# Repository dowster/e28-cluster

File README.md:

# E28 Cluster Driver

E28 Cluster Driver is (going to be...) an ESP32 based driver board which allows the E28, and possibly E21/E30, cluster to be controlled via custom inputs. For the first version custom input will be done solely via CAN Bus. There won't be any hardcoded message spec, that will be configurable by the user after firmware has been flashed. 

> Main repository is at https://gitlab.com/dowster/e28-cluster

# Build Status

## Hardware

- ESP32
- [GD32VF103RBT6](https://www.mouser.com/ProductDetail/GigaDevice/GD32VF103RBT6)

# ESP IDF Version
v4.2

:)

# E28 Cluster Driver Inputs

Input to the E28 cluster driver shall be done via CAN Bus and possibly with a web based interface for diagnostics, calibration, and configuration. The CAN input shall be configurable so that any value on a can message may be mapped to any of the outputs, allowing the potential for configuring the driver with custom cluster gauge faces. IE: using the econometer to show watts / mile. 

# Instrument Cluster Outputs

## Speedometer Output

The speedometer of the E28 cluster is pulse driven. Approximately 2Hz for every MPH. IE: 50hz -> 25mph, 280hz -> 140mph. Driving the speedometer will advance the odometer automatically. It will also generate a pulse signal that is output to the SI board and the cruise control hardware. 

The speedometer operates on a [UAF 2115 IC](https://darisusgmbh.de/darisus/Elektonikshop/Datenblaetter/ITT/UAF2115.pdf). This IC is a general purpose speedoemter and mileage indidactor IC by ITT Semiconductors. It provides a constant current source to the output pin(s) 10-13 on the E28 cluster plug C2 (white), these four pins are all bridged together, shorting these to ground will provide a pulse to the speedometer. The UAF 2115 also provides an open collector NPN pulse output to drive things such as cruise control. In order to trigger a pulse the speed sensor in the differential would short to ground as each tooth of the gear passed by, these pulses must be atleast 50 microseconds in duration, the max frequency is 10Khz. On the E28 Pin 11 of UAF 2115 is connected to ground, so the division factor is 2^6, I think this is to configure how the odometer tracks distance. 

## Temperature Gauge Output

The temperature guage output will be an open collector NPN output from the E28 cluster driver. The temperature gauge is controlled by varying the current output of pin 12 on connector C1 of the E28 instrument cluster. To control this I'll either use the DAC on the ESP32 or use PWM. I have had some issues with "buzzing" when using PWM but I may just need a higher frequency. 

## Fuel Gauge Output

This is pretty much the same as the temperature gauge but with a different calibration. I'll be using a lower value resistor on the gate of this transistor since the fuel gauge requires more current. This signal is also output to the onboard computer by default. See [OBC Outputs](#OBC-Outputs) for information on how I plan to control the OBC.

## Tachometer Output

The tachometer is controleld by a simple voltage input. I'm thinking a PNP driver for this with PWM control should be fine. 

## Econometer Output

No clue how to do this one yet, haven't really looked into it. 

## Warning Indicators (On PCB)

The warning lights will be controlled via simple solid state relay circuits. Either PNP or NPN transistors controleld via shift registers to save up some pins on the ESP32, if needed. Some of the warning indicators are built onto the instrument cluster's PCB, others are controlled via lights have external wiring. 

### Charge Indicator

Could have many different functions, possibly solid when charging the pack or when the pre-charge resistor is engaged and flashing when a pack error is detected.

### Brake Warning Indicator

TODO

### High Beam Indicator

TODO

### Fog Light Indicator

TODO

### LH Turn Indicator

TODO

### RH Turn Indicator

TODO

### Low Fuel Warning Indicator 

TODO

### "Check" Active Check Control Alarm Indicator

TODO

### Oil Pressure Warning Indicator

This is probably not needed with an EV so that could be modified to be _something else_.

### "Park Brake" Indicator

TODO

### Brake Lining indicator

Haven't seen how this wires up yet, It's on the PCB.

## Warning Indicators (External Wiring)

### Left and Right turn arrows

Probably used to be used on cars where there was only one lamp to tell you that the turn indicators were on. Could be repurposed with a different logo. Background is green.

### Solid Yellow

There's no graphic on this lamp, it's in the 3rd position from left and just has a yellow or orange color filter. 

### EML

Not wired up, says "EML" in black letters with a yellow or orange color filter. 4th position from left

### Solid Green

No graphic on this indiactor, just a solid green. 6th position from left.

### ABS

If the stock ABS is kept this can stay here. Not sure if ABS is used on many swaps but I think that if it is this light may want to be used as a way to kill regen and let the motor coast while ABS figures out what to do. 

## Gearshift Indicators

Seems like even the manual clusters include this plate, or my car has been swapped with an automatic cluster. 

### Transmission Warning Indicator

Shows as a gear with an exclamation mark in the center

### P, R, N, D

Pretty self explanatory

### 3, 2, 1

Show up as individual lamps, for indicating if you've manually selected one of these gears I presume. 

### 1-2-3

This is on single indicator, I presume that it indicates you've disabled overdrive. 

# OBC Outputs

The method for driving the OBC hasn't been determined yet, two options are to just plug the OBC into the instrument cluster and let it run business as usual. The more involved, and possibly better method is to map out the pins on the OBC and manipulate that with the  E28 cluster driver. The main feature I'd like to see out of this is an accuruate range estimate based on pack state of charge and average watts/mile.

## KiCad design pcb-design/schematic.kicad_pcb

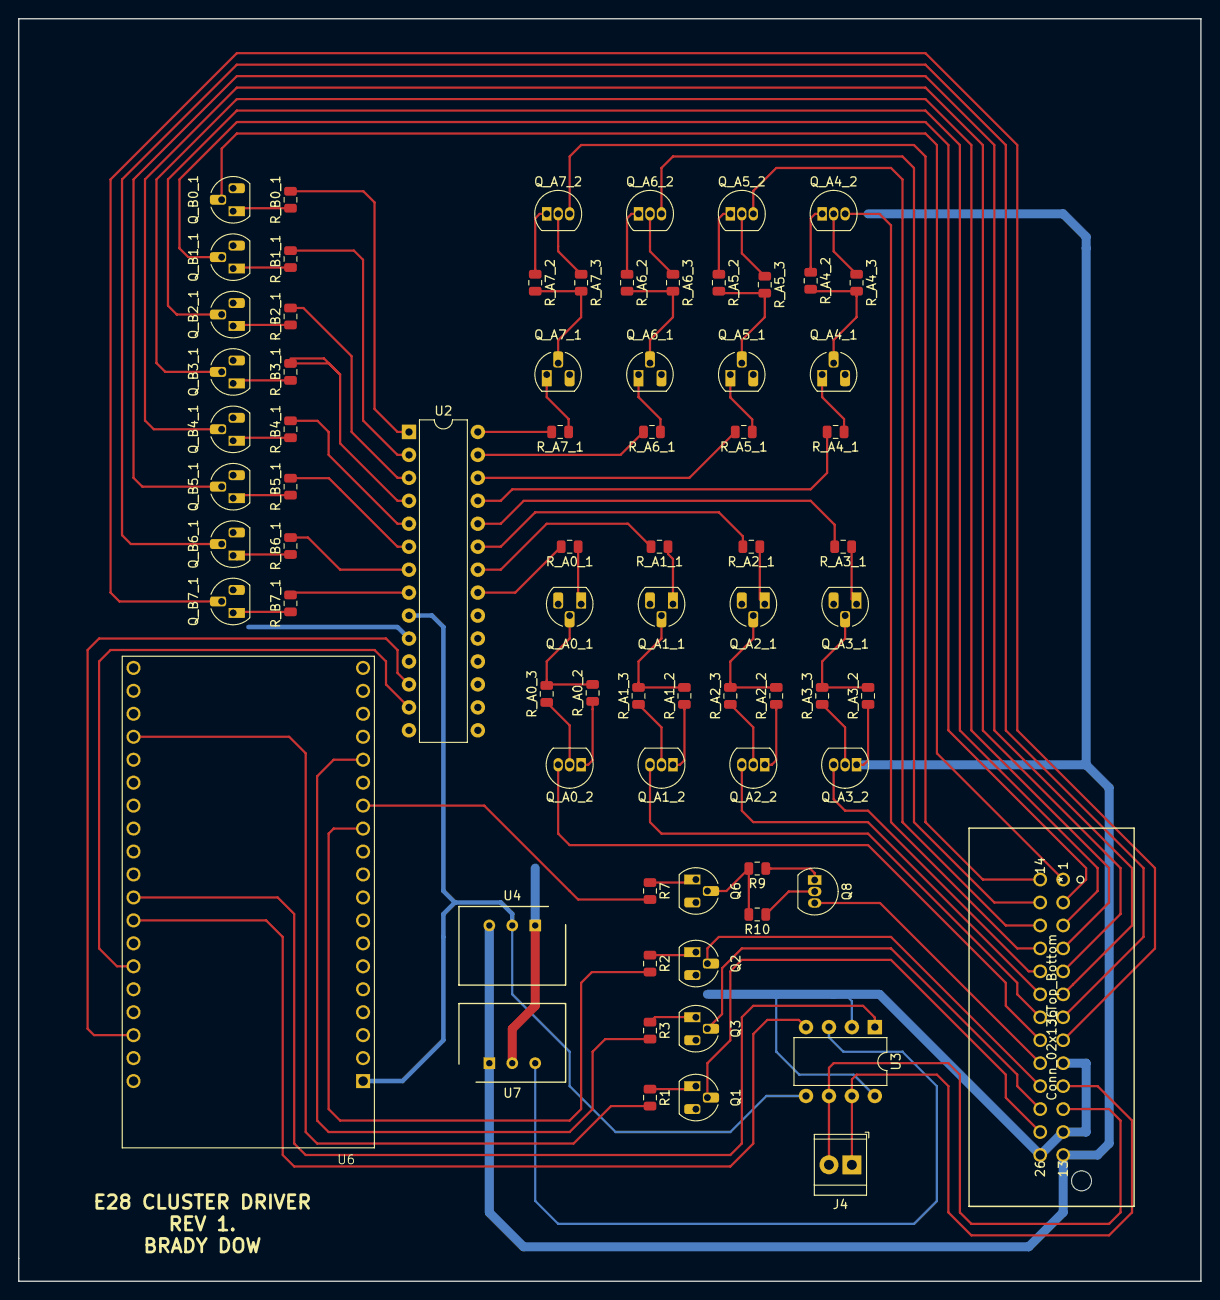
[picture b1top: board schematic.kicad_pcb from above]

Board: 2 copper layers, 130.8 x 139.7 mm, 74 parts (0 on the bottom side), 88 nets.

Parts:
J4: Screw_Terminal_01x02; TerminalBlock_TE_282834-2_1x02_P2.54mm_Horizontal
J6: Conn_02x13_Top_Bottom; Connector_TE_827881-1
Q1, Q2, Q3, Q6: 2N2222; TO-92_HandSolder
Q8: 2N3906; TO-92_Inline
Q_A0_1, Q_A1_1, Q_A2_1, Q_A3_1, Q_A4_1, Q_A5_1, Q_A6_1, Q_A7_1: 2N2222; TO-92_HandSolder
Q_A0_2, Q_A1_2, Q_A2_2, Q_A3_2, Q_A4_2, Q_A5_2, Q_A6_2, Q_A7_2: 2N3906; TO-92_Inline
Q_B0_1, Q_B1_1, Q_B2_1, Q_B3_1, Q_B4_1, Q_B5_1, Q_B6_1, Q_B7_1: 2N2222; TO-92_HandSolder
R1, R3: 470; R_0805_2012Metric
R2: 220; R_0805_2012Metric
R7, R10: 4700; R_0805_2012Metric
R9: 22000; R_0805_2012Metric
R_A0_1, R_A0_3, R_A1_1, R_A1_3, R_A2_1, R_A2_3, R_A3_1, R_A3_3, R_A4_1, R_A4_3, R_A5_1, R_A5_3, R_A6_1, R_A6_3, R_A7_1, R_A7_3: 4700; R_0805_2012Metric
R_A0_2, R_A1_2, R_A2_2, R_A3_2, R_A4_2, R_A5_2, R_A6_2, R_A7_2: 22000; R_0805_2012Metric
R_B0_1, R_B1_1, R_B2_1, R_B3_1, R_B4_1, R_B5_1, R_B6_1, R_B7_1: 4700; R_0805_2012Metric
U2: MCP23017_SP; DIP-28_W7.62mm
U3: MCP2562-E-P; DIP-8_W7.62mm
U4: AP1117-33; SIP3_11.6x8.5mm
U6: ESP32-DEVKITC-32D; MODULE_ESP32-DEVKITC-32D
U7: L7805; SIP3_11.6x8.5mm

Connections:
+3V3: U2.9, U3.5, U4.2, U6.1
+5V: U3.3, U7.3
+12V: J6.13, Q8.1, Q_A0_2.1, Q_A1_2.1, Q_A2_2.1, Q_A3_2.1, Q_A4_2.1, Q_A5_2.1, Q_A6_2.1, Q_A7_2.1, R9.1, R_A0_2.1, R_A1_2.1, R_A2_2.1, R_A3_2.1, R_A4_2.1, R_A5_2.1, R_A6_2.1, R_A7_2.1, U4.3, U7.1
A0_SourceOutput: J6.21, Q_A0_2.3
A1_SourceOutput: J6.20, Q_A1_2.3
A2_SourceOutput: J6.19, Q_A2_2.3
A3_SourceOutput: J6.18, Q_A3_2.3
A4_SourceOutput: J6.17, Q_A4_2.3
A5_SourceOutput: J6.16, Q_A5_2.3
A6_SourceOutput: J6.15, Q_A6_2.3
A7_SourceOutput: J6.14, Q_A7_2.3
B0_SinkOutput: J6.1, Q_B0_1.2
B1_SinkOutput: J6.2, Q_B1_1.2
B2_SinkOutput: J6.3, Q_B2_1.2
B3_SinkOutput: J6.4, Q_B3_1.2
B4_SinkOutput: J6.5, Q_B4_1.2
B5_SinkOutput: J6.6, Q_B5_1.2
B6_SinkOutput: J6.7, Q_B6_1.2
B7_SinkOutput: J6.8, Q_B7_1.2
CAN0_H: J4.1, J6.10, U3.7
CAN0_L: J4.2, J6.11, U3.6
ESP_CAN0_RX: U3.4, U6.27
ESP_CAN0_TX: U3.1, U6.28
FuelGauge: J6.23, Q2.2
FuelOutput: R2.2, U6.12
GND: J6.9, J6.12, J6.26, Q1.3, Q2.3, Q3.3, Q6.3, Q_A0_1.3, Q_A1_1.3, Q_A2_1.3, Q_A3_1.3, Q_A4_1.3, Q_A5_1.3, Q_A6_1.3, Q_A7_1.3, Q_B0_1.3, Q_B1_1.3, Q_B2_1.3, Q_B3_1.3, Q_B4_1.3, Q_B5_1.3, Q_B6_1.3, Q_B7_1.3, U2.10, U2.15, U2.16, U2.17, U3.2, U3.8, U4.1, U6.14, U6.20, U6.26, U7.2
I2C0_SCK: U2.12, U6.22
I2C0_SDA: U2.13, U6.25
unnamed: Q1.1, R1.1
unnamed: Q2.1, R2.1
unnamed: Q3.1, R3.1
unnamed: Q6.1, R7.1
unnamed: Q6.2, R9.2, R10.2
unnamed: Q8.2, R10.1
unnamed: Q_A0_1.1, R_A0_1.1
unnamed: Q_A0_1.2, R_A0_2.2, R_A0_3.2
unnamed: Q_A0_2.2, R_A0_3.1
unnamed: Q_A1_1.1, R_A1_1.1
unnamed: Q_A1_1.2, R_A1_2.2, R_A1_3.2
unnamed: Q_A1_2.2, R_A1_3.1
unnamed: Q_A2_1.1, R_A2_1.1
unnamed: Q_A2_1.2, R_A2_2.2, R_A2_3.2
unnamed: Q_A2_2.2, R_A2_3.1
unnamed: Q_A3_1.1, R_A3_1.1
unnamed: Q_A3_1.2, R_A3_2.2, R_A3_3.2
unnamed: Q_A3_2.2, R_A3_3.1
unnamed: Q_A4_1.1, R_A4_1.1
unnamed: Q_A4_1.2, R_A4_2.2, R_A4_3.2
unnamed: Q_A4_2.2, R_A4_3.1
unnamed: Q_A5_1.1, R_A5_1.1
unnamed: Q_A5_1.2, R_A5_2.2, R_A5_3.2
unnamed: Q_A5_2.2, R_A5_3.1
unnamed: Q_A6_1.1, R_A6_1.1
unnamed: Q_A6_1.2, R_A6_2.2, R_A6_3.2
unnamed: Q_A6_2.2, R_A6_3.1
unnamed: Q_A7_1.1, R_A7_1.1
unnamed: Q_A7_1.2, R_A7_2.2, R_A7_3.2
unnamed: Q_A7_2.2, R_A7_3.1
unnamed: Q_B0_1.1, R_B0_1.1
unnamed: Q_B1_1.1, R_B1_1.1
unnamed: Q_B2_1.1, R_B2_1.1
unnamed: Q_B3_1.1, R_B3_1.1
unnamed: Q_B4_1.1, R_B4_1.1
unnamed: Q_B5_1.1, R_B5_1.1
unnamed: Q_B6_1.1, R_B6_1.1
unnamed: Q_B7_1.1, R_B7_1.1
unnamed: R_A0_1.2, U2.21
unnamed: R_A1_1.2, U2.22
unnamed: R_A2_1.2, U2.23
unnamed: R_A3_1.2, U2.24
unnamed: R_A4_1.2, U2.25
unnamed: R_A5_1.2, U2.26
unnamed: R_A6_1.2, U2.27
unnamed: R_A7_1.2, U2.28
unnamed: R_B0_1.2, U2.1
unnamed: R_B1_1.2, U2.2
unnamed: R_B2_1.2, U2.3
unnamed: R_B3_1.2, U2.4
unnamed: R_B4_1.2, U2.5
unnamed: R_B5_1.2, U2.6
unnamed: R_B6_1.2, U2.7
unnamed: R_B7_1.2, U2.8
Speedometer: J6.24, Q3.2
SpeedometerSignal: R3.2, U6.15
Tachometer: J6.22, Q8.3
TachometerOutput: R7.2, U6.13
TempGauge: J6.25, Q1.2
TemperatureOutput: R1.2, U6.35

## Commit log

2019-08-21 First Build
2019-11-16 I guess i moved something...
2019-11-21 Added the circuit for driving the speedometer pulses. Speedometer pulse is approximately 2hz for every mph. Minimum is around 10-20hz.
2019-11-24 Created a README to define some of the project scope and maybe force myself to complete this one.
2019-11-24 Fix the link to OBC Outputs
2019-11-25 Started pulling out fuel gauge stuff. Mainly committing to transfer this to my desktop.
2019-11-25 Schematic updates, learning KiCad a bit.
2019-11-26 Stubbed out fuel and temp gauges more. Started on speedometer gauge.
2019-12-06 trying some CI stuff
2019-12-06 Update README.md
    Added travis.ci build status
2019-12-06 more travis CI
2019-12-06 travis ci, again
2019-12-06 Tachometer Gauge Split to it's own file
2019-12-06 try 3
2019-12-15 Add defines for the mcp23017 registers. Update the fuel gauge logging to be more clear. Start on the indicator lights.
2019-12-15 param not parm, this isn't cobol.
2019-12-16 Fill out the functions for the indicator lights portion.
    Include link to the MCP23017 datasheet in the header. Link will probably die tomorrow.
2019-12-16 Adding vscode settings to gitignore.
2019-12-16 i think i fixed some whoopsies but my local compiler seems either broken or out of date.
2019-12-17 Added can message parsing for @tomdebree's simpbms
2019-12-17 Added Tachometer circuit to schematic
2019-12-17 Version locked the build container. I guess latest is past v4.0 now
2020-01-05 Including the Adafruit driver for the i2c gpio expander as a reference.
2020-01-07 Switching defines to static vars, moved i2c to NUM 1
2020-01-07 Back to 0 with no ack
2020-01-31 Not sure what's going on anymore
2020-02-23 Got mcp23017 working with another library. I don't think I'm using I2C correctly in my own solution.
2020-02-23 V3.2.2 doesn't have a docker image so switching to v3.3.1
2020-02-23 Naming conventions are hard.
2020-02-23 Will this add the submodule?
2020-02-23 Mayyyybe now
2020-02-24 Got this working with IDF v4.0
2020-02-29 Put the mcp23017 library into indicator lights.
2020-02-29 Split things out into header files.
2020-02-29 Indicator lights i2c debugging (#1)
    i2c has been debugged. The main issue was probably me not re-initing the i2c driver properly and even with the library I pulled in I need to make the first config call twice to account for a corrupt 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
    * Got this working with IDF v4.0
    * Put the mcp23017 library into indicator lights.
    * Split things out into header files.
2020-02-29 Removed files that should never have been in the repo.
2020-02-29 Add .gitlab-ci.yml
2020-02-29 Add submodule strategy for gitlab pipeline builds.
2020-02-29 Incorrect path on where the tar file is going.
2020-03-05 Added lots of extern "C" Converted the main and temp gauge to C++
2020-03-10 Add initial attempt at generating schematics
2020-03-10 Add tag to eeshow image
2020-03-10 Can only be one project file
2020-03-10 Schematic is an unknown file type
2020-03-10 pcb-design.pro didn't have an associated pcb-design.sch. Trying schematic.
2020-03-10 add the schematic cache library, might contain components.
2020-03-10 uncomment code build
2020-03-10 add -e, see: https://neo900.org/git/eeshow/plain/README
2020-03-10 Use custom image
2020-03-10 Switch to use latest image eeshow
2020-03-10 Update travis ci and hope registry is available
2020-03-10 Switch travis ci to add multiple files to the release
2020-03-10 Shrink tar gzip artifact
2020-03-10 Try multi line again!
2020-03-10 eh just tag it
2020-03-11 More slashes
2020-03-11 Changed the script multi line chracter
2020-03-14 Don't track the workspace file and don't track .sch-bak data.
    Created a schematic for the indicator lights circuit.
2020-03-14 Add caching to the gitlab builds, might break reproducibility but it should speed em up. Release builds will need to not use the cache.
2020-03-22 Checking in schematic files
2020-03-22 Added build artifact caching to travis builds
2020-03-28 Add some wifi client code so that I can start working on the http server for this.
2020-04-19 Added basic wifi functionality added a variable to store temp gauge position added map to hold strings for indicator lights
2020-04-19 Need to update sdkconfig to fix some update issues.
2020-04-20 Stopgap to keep builds working until PR 5148 is merged in esp-idf
2020-04-20 Indicator flash was only flashing half of the outputs.
2020-05-01 Add some mdns advertising. Not yet working
2020-05-02 Moved some files around
2020-05-05 Swapped the esp32 symbol and footprint to be one for the dev modules so I can just populate the boards with standoffs.
    Wired up some more nets and made the layout a little prettier.
2020-06-09 checkin
2020-06-09 Added TE 827881-1 connector and footprint re-arranged schematic
2020-06-10 Final changes for Rev 1 board, ordered 10/06/2020
2020-06-14 Updated resistor footprints to 0805 which had better coverage for JLCPCB basic parts.
2020-06-14 Trying to add a pdf of the pcb layout
2020-06-14 Revert "Trying to add a pdf of the pcb layout"
    This reverts commit b56f1969f75d8c114cc69d4ada7bfdc8b18707b8.
2023-02-14 chore: add link to main repo on gitlab
2023-02-14 feat: add local build script because reasons
2023-02-14 add potential backup MCU
2023-02-14 Squashed commit of the following:
    commit 3feebbdd7fc9a19dcfe87aea05ec82215f171dbb
    Author: dowster <brady@dowster.net>
    Date: Mon Feb 13 23:49:32 2023 -0600
    add potential backup MCU
    commit 7657e025624eaa3ad175eda664276684d823e8da
    Author: dowster <brady@dowster.net>
2025-11-06 feat: migrate to github actions and add a GEMINI.md file
2025-11-06 ignore macos .DS_Store file

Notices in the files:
parts and their libraries:
Copyright 2016 Accelerated Designs. All rights reserved.
